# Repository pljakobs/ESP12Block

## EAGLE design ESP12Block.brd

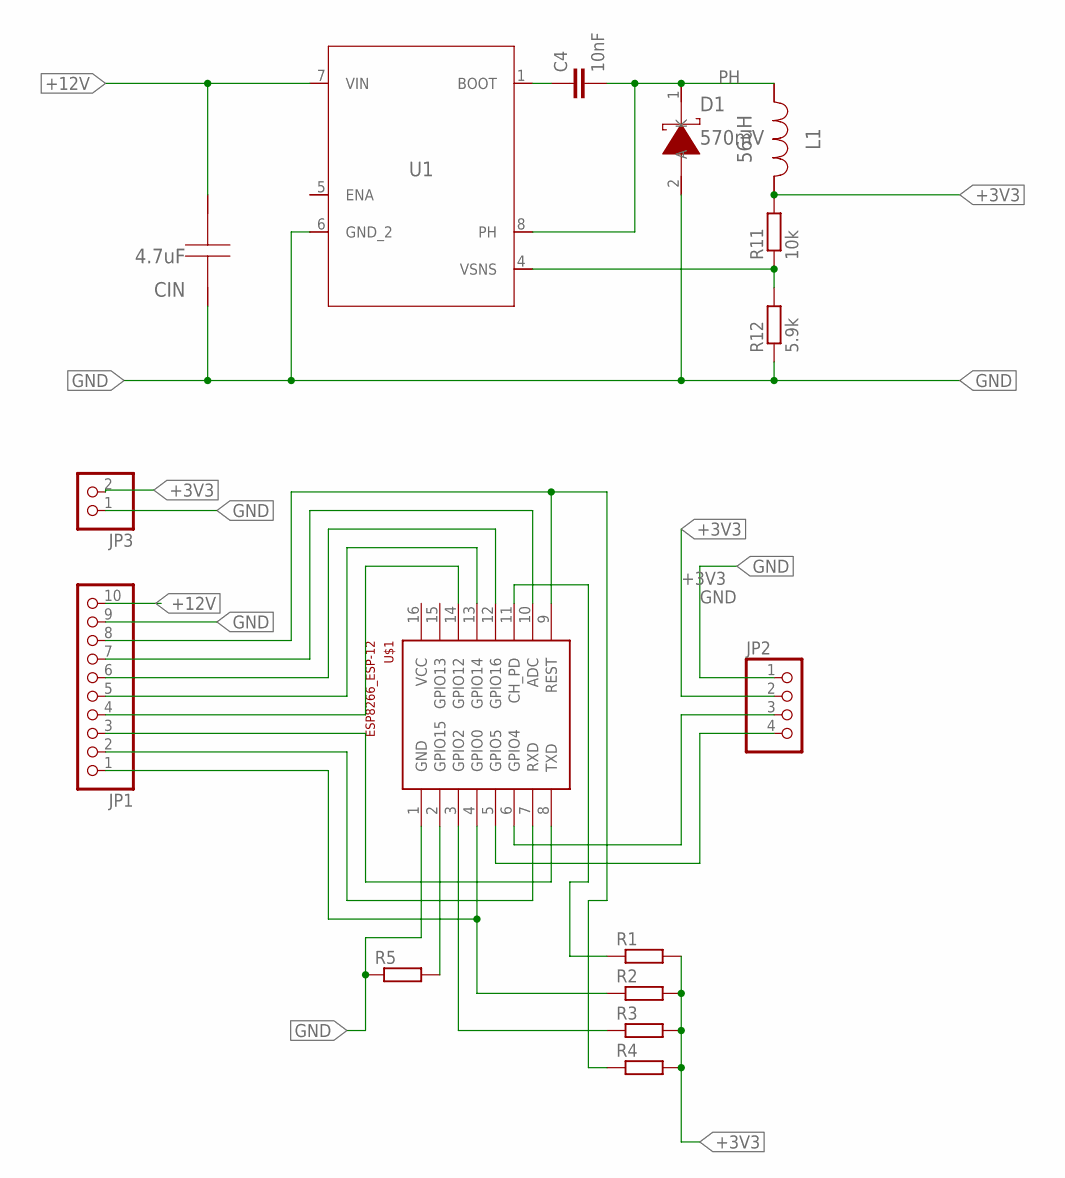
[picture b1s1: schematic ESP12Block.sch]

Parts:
C4: 10nF; C0805
CIN: 4.7uF; 1206
D1: 570mV; SOD-123F
JP1: PINHD-1X10_2.00; 1X10M
JP2: PINHD-1X4_2.54; 1X04
JP3: PINHD-1X2M; 1X02M
L1: 56uH; IND_NPI75C
R1, R2, R3, R4, R5: R-EU_M0805; M0805
R11: 10k; R0805
R12: 5.9k; R0805
U1: TPS5410DR; M08A
U$1: ESP8266_ESP-12; ESP8266-ESP12

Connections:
+3V3: JP2.2, JP3.2, L1.1, R1.2, R2.2, R3.2, R4.2, R11.2
+12V: CIN.2, JP1.10, U1.7 (VIN)
ADC: JP1.7, U$1.10 (ADC)
BOOT: C4.1, U1.1 (BOOT)
CH_PD: R1.1, U$1.11 (CH_PD)
GND: CIN.1, D1.2 (A), JP1.9, JP2.1, JP3.1, R5.1, R12.1, U1.6 (GND_2), U$1.1 (GND)
GPIO0: JP1.1, R2.1, U$1.4 (GPIO0)
GPIO2: R3.1, U$1.3 (GPIO2)
GPIO4: JP2.3, U$1.6 (GPIO4)
GPIO5: JP2.4, U$1.5 (GPIO5)
GPIO12: JP1.4, U$1.14 (GPIO12)
GPIO14: JP1.5, U$1.13 (GPIO14)
GPIO15: R5.2, U$1.2 (GPIO15)
GPIO16: JP1.6, U$1.12 (GPIO16)
PH: C4.2, D1.1 (K), L1.2, U1.8 (PH)
RST: JP1.8, R4.1, U$1.9 (REST)
RXD: JP1.2, U$1.7 (RXD)
SENS: R11.1, R12.2, U1.4 (VSNS)
TXD: JP1.3, U$1.8 (TXD)

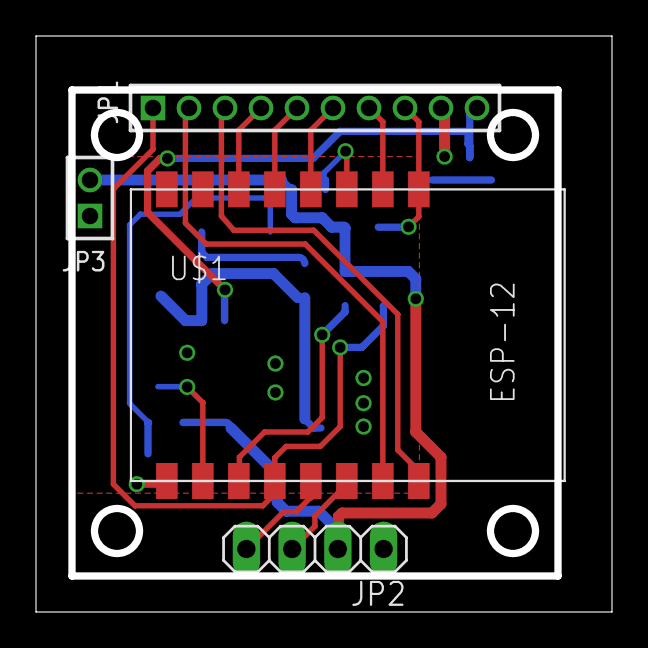
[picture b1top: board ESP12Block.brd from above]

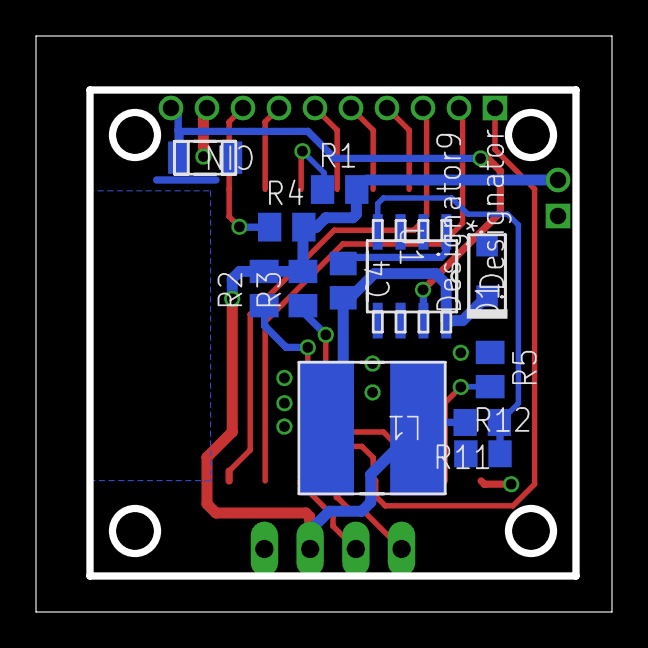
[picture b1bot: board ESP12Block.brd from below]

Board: 2 copper layers, 31.6 x 31.6 mm, 16 parts (12 on the bottom side), 19 nets.

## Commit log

2017-11-28 initial commit
    a very small ESP12 Platform
2017-12-10 trying a different orientation
    doesn't quite work out for the 3V3 rail
2017-12-10 minor changes
    improved the 3.3V and GND paths
2017-12-10 fixed some DRC errors
    I have ignored the dimension errors
